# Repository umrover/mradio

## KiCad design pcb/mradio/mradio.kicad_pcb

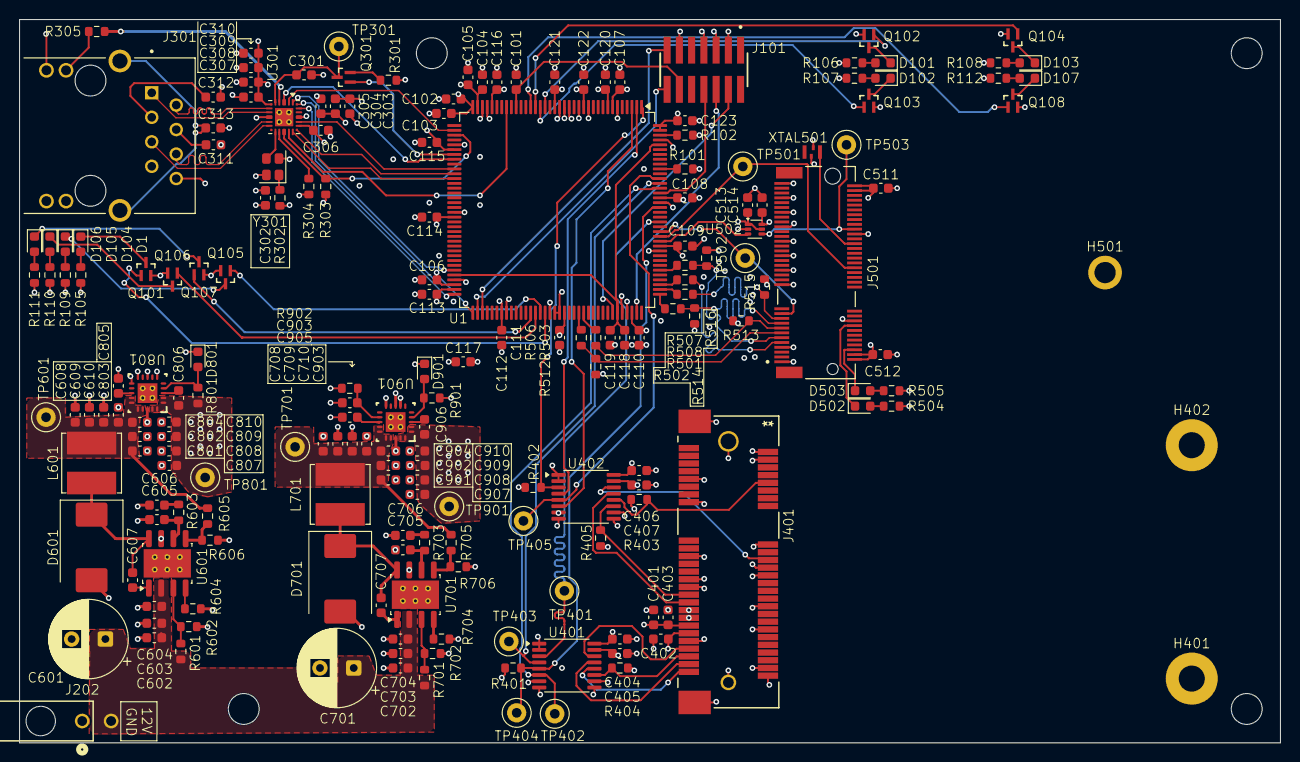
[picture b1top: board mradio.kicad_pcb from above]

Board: 6 copper layers, 130.8 x 75.0 mm, 193 parts (0 on the bottom side), 122 nets.

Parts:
C101, C102, C104, C107, C108, C109, C110, C111, C112, C113, C114, C115, C116, C121, C122, C123, C305, C308, C403, C404, C405, C406, C407, C805, C905: 100nF; C_0603_1608Metric
C103, C105, C120, C304, C309, C402: 1uF; C_0603_1608Metric
C106, C117: 4.7uF; C_0603_1608Metric
C118, C119, C602, C603, C604, C702, C703, C704: 2.2uF; C_0603_1608Metric
C301: 0.01uF; C_0603_1608Metric
C302, C311, C312, C513, C514, C607, C707: 0.1uF; C_0603_1608Metric
C303, C310, C511, C512, C802, C803, C804, C808, C809, C810, C902, C903, C903#2, C904, C908, C909, C910: 10uF; C_0603_1608Metric
C306, C307, C806, C906: 10nF; C_0603_1608Metric
C313: 0nF; C_0603_1608Metric
C401, C608, C609, C610, C708, C709, C710, C801, C807, C901, C907: 47uF; C_0603_1608Metric
C601, C701: 100uF; CP_Radial_D8.0mm_P3.50mm
C605: 100pF; C_0603_1608Metric
C606, C706: 29nF; C_0603_1608Metric
C705: 180pF; C_0603_1608Metric
D1, D101, D102, D103, D104, D105, D106, D107, D502, D503, D801, D901: LED; LED_0603_1608Metric
D601, D701: 60V; D_SMC
H401, H402: MountingHole_Pad; MountingHole_2.7mm_M2.5_Pad
H501: MountingHole_Pad; MountingHole_2.2mm_M2_ISO7380_Pad
J101: Conn_02x07_Odd_Even; SAMTEC_FTSH-107-01-X-DV-K
J202: Conn_01x02; CONN_2125280000_02_MOL
J301: 2250065-1; BEL_2250065-1
J401: MM60-52B1-E1-R650; CONN_MM60-52B1-E1-R650_JAE
J501: MDT420E01001; AMPHENOL_MDT420E01001
L601, L701: 10uH; L_Bourns_SRN6045TA
Q101, Q102, Q103, Q104, Q105, Q106, Q107, Q108: Q_NMOS; SSM_TOS_REAL
Q301: SSM3K56FS_LF; SSM_TOS
R101, R102, R401, R402, R403, R404, R405, R512, R513, R514, R515, R516: 10K; R_0603_1608Metric
R105, R106, R107, R108, R109, R110, R111, R112, R504, R505: 1K; R_0603_1608Metric
R301, R501, R502, R503, R506, R507, R508, R902: 0; R_0603_1608Metric
R302: 70k; R_0603_1608Metric
R303: 2.2k; R_0603_1608Metric
R304: 6.49k; R_0603_1608Metric
R305: 250; R_0603_1608Metric
R601, R701: 442k; R_0603_1608Metric
R602, R702: 90.9k; R_0603_1608Metric
R603: 6.34k; R_0603_1608Metric
R604, R704: 193k; R_0603_1608Metric
R605: 37k; R_0603_1608Metric
R606, R706: 10.2k; R_0603_1608Metric
R703: 3.74k; R_0603_1608Metric
R705: 17.4k; R_0603_1608Metric
R801, R901: 1.2k; R_0603_1608Metric
TP301, TP401, TP402, TP403, TP404, TP405, TP501, TP502, TP503: TestPoint; TestPoint_Loop_D1.80mm_Drill1.0mm_Beaded
TP601: 3v7_TP; TestPoint_Loop_D1.80mm_Drill1.0mm_Beaded
TP701: 2v2_TP; TestPoint_Loop_D1.80mm_Drill1.0mm_Beaded
TP801: 3v3_TP; TestPoint_Loop_D1.80mm_Drill1.0mm_Beaded
TP901: 1v8_TP; TestPoint_Loop_D1.80mm_Drill1.0mm_Beaded
U1: STM32H745ZITx; LQFP-144_20x20mm_P0.5mm
U301: DP83825I; Texas_RMQ0024A_WQFN-24-1EP_3x3mm_P0.4mm_EP1.9x1.9mm
U401, U402: 74AVC4T774; TSSOP-16_4.4x5mm_P0.65mm
U502: SN74LVC1T45DRL; SOT-563
U601, U701: TPS54560BDDA; Texas_R-PDSO-G8_EP2.95x4.9mm_Mask2.4x3.1mm_ThermalVias
U801, U901: TPS7A8500ARGRR; TPS7A8500RGRR
XTAL501: SIT1533AI-H4-DCC-32.768E; XTAL4_SiT1533_SIT
Y301: DSC1525JL2A-25M00000T; Oscillator_SMD_SeikoEpson_SG210-4Pin_2.5x2.0mm

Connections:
+1V8: C102.1, C103.1, C104.1, C105.1, C106.2, C107.1, C108.1, C109.1, C110.1, C111.1, C112.1, C113.1, C114.1, C115.1, C116.1, C117.1, C120.1, C121.1, C122.1, C123.1, C302.1, C303.2, C304.2, C305.2, C306.2, C404.1, C406.1, C513.1, C906.1, C907.1, C908.1, C909.1, C910.1, J101.3, R102.2, R302.1, R303.1, R401.1, R402.1, R512.1, R513.1, R514.1, R515.1, R516.1, TP901.1 (1_1), U1.7 (VDD), U1.8 (VBAT), U1.13 (VDD), U1.19 (VDD), U1.32 (VDD), U1.35 (VREF+), U1.36 (VDDA), U1.42 (VDD), U1.56 (VDD), U1.70 (VDDLDO), U1.71 (VDD), U1.79 (VDD), U1.92 (VDD), U1.105 (VDDLDO), U1.106 (VDD), U1.119 (VDD), U1.129 (VDD), U1.143 (VDDLDO), U1.144 (VDD), U301.19 (VDDIO), U401.1 (DIR1), U401.2 (DIR2), U401.7 (DIR3), U401.16 (V_{CCA}), U402.1 (DIR1), U402.2 (DIR2), U402.16 (V_{CCA}), U502.1 (VCCA), U502.5 (DIR), U901.1 (OUT), U901.2 (SNS), U901.19 (OUT), U901.20 (OUT), Y301.4 (Vcc)
+2V2: C708.1, C709.1, C710.1, C901.1, C902.1, C903#2.1, C904.1, L701.2, R705.1, TP701.1 (1_1), U901.14 (EN), U901.15 (IN), U901.16 (IN), U901.17 (IN)
+3V3: C307.2, C308.2, C309.2, C310.2, C401.1, C402.1, C403.1, C405.1, C407.1, C511.1, C512.1, C514.2, C806.1, C807.1, C808.1, C809.1, C810.1, J401.2 (+3V3AUX), J401.24 (+3V3AUX), J401.39 (+3V3AUX), J401.41 (+3V3AUX), J401.52 (+3V3AUX), J501.2, J501.4, J501.72, J501.74, R105.2, R106.2, R107.2, R108.2, R109.2, R110.2, R111.2, R112.2, R403.1, R404.1, R504.1, R505.1, R801.2, R901.2, R902.1, TP801.1 (1_1), U1.90 (VDD50_USB), U1.91 (VDD33_USB), U301.6 (VDDA3V3), U401.15 (V_{CCB}), U402.15 (V_{CCB}), U502.6 (VCCB), U801.1 (OUT), U801.2 (SNS), U801.19 (OUT), U801.20 (OUT), XTAL501.4 (Vdd)
+3V7: C608.1, C609.1, C610.1, C801.1, C802.1, C803.1, C804.1, L601.2, R605.1, TP601.1 (1_1), U801.14 (EN), U801.15 (IN), U801.16 (IN), U801.17 (IN)
+12V: C601.1, C602.1, C603.1, C604.1, C701.1, C702.1, C703.1, C704.1, J202.2, R601.1, R701.1, U601.2 (VIN), U701.2 (VIN)
/2.4-5 Ghz/M2_WL_REG_ON: J501.56, TP503.1 (1_1), U502.4 (B)
/2.4-5 Ghz/SDIO_CK: J501.9, R508.1
/2.4-5 Ghz/SDIO_CMD: J501.11, R507.1, R516.2
/2.4-5 Ghz/SDIO_D0: J501.13, R506.1, R512.2
/2.4-5 Ghz/SDIO_D1: J501.15, R503.1, R513.2
/2.4-5 Ghz/SDIO_D2: J501.17, R502.1, R514.2
/2.4-5 Ghz/SDIO_D3: J501.19, R501.1, R515.2
/900 Mhz/SPI1_CS_3V3: J401.51 (Reserved), U401.12 (B3)
/900 Mhz/SPI1_MISO_3V3: J401.47 (Reserved), R404.2, U401.11 (B4)
/900 Mhz/SPI1_MOSI_3V3: J401.49 (Reserved), U401.13 (B2)
/900 Mhz/SPI1_SCK_3V3: J401.45 (Reserved), U401.14 (B1)
/900 Mhz/SPI_INT_3V3: J401.10 (UIM_DATA), R403.2, U402.12 (B3)
/900 Mhz/WM_BUSY_3V3: J401.31 (PETn0), R405.2, U402.11 (B4)
/900 Mhz/WM_RESET_3V3: J401.22 (~PERST), U402.14 (B1)
/900 Mhz/WM_WAKE_3V3: J401.33 (PETp0), U402.13 (B2)
/Ethernet/ETH_LINK: R305.2, U301.4 (LED0/S(ANEG_Dis))
/Ethernet/ETH_RD+: J301.1 (RDP), U301.8 (RD+)
/Ethernet/ETH_RD-: J301.2 (RDN), U301.7 (RD-)
/Ethernet/ETH_TD+: J301.5 (TDP), U301.11 (TD+)
/Ethernet/ETH_TD-: J301.6 (TDN), U301.10 (TD-)
/MCU/BOOT0: R101.1, U1.135 (BOOT0)
/MCU/M4_DBG1: Q102.G, U1.21 (PF7)
/MCU/M4_DBG2: Q103.G, U1.22 (PF8)
/MCU/M7_DBG1: Q104.G, U1.23 (PF9)
/MCU/M7_DBG2: Q108.G, U1.24 (PF10)
/MCU/NRST: C101.1, J101.12, U1.27 (NRST)
/MCU/STLINK_RX: J101.13, U1.75 (PB15)
/MCU/STLINK_TX: J101.14, U1.74 (PB14)
/MCU/SWCLK: J101.6, U1.107 (PA14)
/MCU/SWDIO: J101.4, U1.102 (PA13)
/MCU/SWO: J101.8, U1.130 (PB3)
/MCU/SoS_LED1: Q107.G, U1.85 (PD15)
/MCU/SoS_LED2: Q106.G, U1.86 (PG6)
/MCU/SoS_LED3: Q105.G, U1.87 (PG7)
/MCU/SoS_LED4: Q101.G, U1.88 (PG8)
/MCU/VCAP: C118.1, C119.1, U1.68 (VCAP), U1.103 (VCAP), U1.140 (VCAP)
/Power Distribution/2v2_Buck/FB: R705.2, R706.1, U701.5 (FB)
/Power Distribution/3v7_Buck/FB: R605.2, R606.1, U601.5 (FB)
ETH_CRS_DV: U1.46 (PA7), U301.20 (CRS_DV/S(PhyAdd[1]))
ETH_INT: U1.44 (PA5), U301.3 (INTR/~PWRDN)
ETH_MDC: U1.29 (PC1), U301.16 (MDC)
ETH_MDIO: R303.2, U1.39 (PA2), U301.15 (MDIO)
ETH_REF_CLK: U1.38 (PA1), U301.2 (50MHzOut/LED2/S(RX_DV_EN))
ETH_RESET: Q301.1 (G), U1.43 (PA4)
ETH_RXD0: U1.47 (PC4), U301.18 (RX_D0/S(PhyAdd[0]))
ETH_RXD1: U1.48 (PC5), U301.17 (RX_D1/S(Master/Slave))
ETH_TXD0: U1.72 (PB12), U301.23 (TX_D0)
ETH_TXD1: U1.73 (PB13), U301.24 (TX_D1)
ETH_TX_EN: U1.67 (PB11), U301.1 (TX_EN)
GND: C101.2, C102.2, C103.2, C104.2, C105.2, C106.1, C107.2, C108.2, C109.2, C110.2, C111.2, C112.2, C113.2, C114.2, C115.2, C116.2, C117.2, C118.2, C119.2, C120.2, C121.2, C122.2, C123.2, C301.2, C302.2, C303.1, C304.1, C305.1, C306.1, C307.1, C308.1, C309.1, C310.1, C311.1, C312.1, C313.2, C401.2, C402.2, C403.2, C404.2, C405.2, C406.2, C407.2, C511.2, C512.2, C513.2, C514.1, C601.2, C602.2, C603.2, C604.2, C605.2, C606.2, C608.2, C609.2, C610.2, C701.2, C702.2, C703.2, C704.2, C705.2, C706.2, C708.2, C709.2, C710.2, C801.2, C802.2, C803.2, C804.2, C805.2, C807.2, C808.2, C809.2, C810.2, C901.2, C902.2, C903.2, C903#2.2, C904.2, C905.2, C907.2, C908.2, C909.2, C910.2, D601.2 (A), D701.2 (A), D801.1 (K), D901.1 (K), H401.1 (1_1), H402.1 (1_1), H501.1 (1_1), J101.5, J101.7, J101.11, J202.1, J301.8 (GND), J301.10, J401.4 (GND), J401.9 (GND), J401.15 (GND), J401.18 (GND), J401.21 (GND), J401.26 (GND), J401.27 (GND), J401.29 (GND), J401.34 (GND), J401.35 (GND), J401.37 (GND), J401.40 (GND), J401.43 (GND), J401.50 (GND), J401.MP, J501.1, J501.7, J501.18, J501.33, J501.39, J501.45, J501.51, J501.54, J501.57, J501.63, J501.69, J501.75, Q101.S, Q102.S, Q103.S, Q104.S, Q105.S, Q106.S, Q107.S, Q108.S, R101.2, R301.2, R304.2, R405.1, R602.2, R604.2, R606.2, R702.2, R704.2, R706.2, U1.6 (VSS), U1.12 (VSS), U1.14 (VSSSMPS), U1.16 (VDDSMPS), U1.17 (VFBSMPS), U1.18 (VSS), U1.33 (VSS), U1.34 (VSSA), U1.41 (VSS), U1.55 (VSS), U1.69 (VSS), U1.80 (VSS), U1.89 (VSS), U1.104 (VSS), U1.118 (VSS), U1.128 (VSS), U1.141 (VSS), U301.9 (GND), U301.21 (GND), U301.25 (GND), U401.8 (DIR4), U401.9 (~OE), U401.10 (GND), U402.7 (DIR3), U402.8 (DIR4), U402.9 (~OE), U402.10 (GND), U502.2 (GND), U601.7 (GND), U601.9 (GND), U701.7 (GND), U701.9 (GND), U801.6 (100_mV), U801.8 (GND), U801.10 (800_mV), U801.11 (1.6_V), U801.18 (GND), U801.21 (PAD), U901.7 (200_mV), U901.8 (GND), U901.10 (800_mV), U901.18 (GND), U901.21 (PAD), XTAL501.2 (GND), Y301.2 (GND)
unnamed: C606.1, R603.1
unnamed: C706.1, R703.1
unnamed: D1.2 (A), R105.1
unnamed: D1.1 (K), Q101.D
unnamed: D101.2 (A), R106.1
unnamed: D101.1 (K), Q102.D
unnamed: D102.2 (A), R107.1
unnamed: D102.1 (K), Q103.D
unnamed: D103.2 (A), R108.1
unnamed: D103.1 (K), Q104.D
unnamed: D104.2 (A), R109.1
unnamed: D104.1 (K), Q105.D
unnamed: D105.2 (A), R110.1
unnamed: D105.1 (K), Q106.D
unnamed: D106.2 (A), R111.1
unnamed: D106.1 (K), Q107.D
unnamed: D107.2 (A), R112.1
unnamed: D107.1 (K), Q108.D
unnamed: D502.2 (A), R504.2
unnamed: D502.1 (K), J501.16
unnamed: D503.2 (A), R505.2
unnamed: D503.1 (K), J501.6
unnamed: C607.2, D601.1 (K), L601.1, U601.8 (SW)
unnamed: C707.2, D701.1 (K), L701.1, U701.8 (SW)
unnamed: D801.2 (A), R801.1, U801.4 (PG)
unnamed: D901.2 (A), R901.1, U901.4 (PG)
unnamed: J301.9, R305.1
unnamed: C312.2, J301.3 (RCT)
unnamed: C313.1, J301.SH1 (SHIELD), J301.SH2 (SHIELD__1)
unnamed: C311.2, J301.4 (TCT)
unnamed: C301.1, Q301.3 (D), TP301.1 (1_1), U301.5 (~RST)
unnamed: Q301.2 (S), R301.1
unnamed: R102.1, U1.142 (PDR_ON)
unnamed: R304.1, U301.14 (RBIAS)
unnamed: U301.13 (XI/50MHzIn), Y301.3 (OUT)
unnamed: C607.1, U601.1 (BOOT)
unnamed: C605.1, R603.2, U601.6 (COMP)
unnamed: R601.2, R602.1, U601.3 (EN)
unnamed: R604.1, U601.4 (RT/CLK)
unnamed: C707.1, U701.1 (BOOT)
unnamed: C705.1, R703.2, U701.6 (COMP)
unnamed: R701.2, R702.1, U701.3 (EN)
unnamed: R704.1, U701.4 (RT/CLK)
unnamed: C806.2, U801.3 (FB)
unnamed: C805.1, U801.13 (NR_SS)
unnamed: C903.1, R902.2, U901.12 (BIAS)
unnamed: C906.2, U901.3 (FB)
unnamed: C905.1, U901.13 (NR_SS)
unnamed: J501.50, XTAL501.3 (CLK_Out)
unnamed: R302.2, Y301.1 (OE)
SDMMC1_CK: R508.2, U1.111 (PC12)
SDMMC1_CMD: R507.2, U1.114 (PD2)
SDMMC1_D0: R506.2, U1.95 (PC8)
SDMMC1_D1: R503.2, U1.96 (PC9)
SDMMC1_D2: R502.2, U1.109 (PC10)
SDMMC1_D3: R501.2, U1.110 (PC11)
SPI1_CS: R401.2, TP404.1 (1_1), U1.127 (PG14), U401.5 (A3)
SPI1_MISO: TP402.1 (1_1), U1.131 (PB4), U401.6 (A4)
SPI1_MOSI: TP403.1 (1_1), U1.132 (PB5), U401.4 (A2)
SPI1_SCK: TP401.1 (1_1), U1.124 (PG11), U401.3 (A1)
SPI_INT: TP405.1 (1_1), U1.133 (PB6), U402.5 (A3)
WL_DEV_WAKE: J501.40, TP501.1 (1_1), U1.121 (PD7)
WL_HOST_WAKE: J501.21, TP502.1 (1_1), U1.122 (PG9)
WL_REG_ON: U1.120 (PD6), U502.3 (A)
WM_BUSY: U1.3 (PE4), U402.6 (A4)
WM_RESET: R402.2, U1.1 (PE2), U402.3 (A1)
WM_WAKE: U1.2 (PE3), U402.4 (A2)

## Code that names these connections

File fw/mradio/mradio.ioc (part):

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Mcu.Name=STM32H745ZITx
Mcu.Package=LQFP144
Mcu.UserName=STM32H745ZITx
PA1.GPIOParameters=PinAttribute,GPIO_Speed_Default_HIGH
PA1.GPIO_Speed_Default_HIGH=GPIO_SPEED_FREQ_VERY_HIGH
PA1.Mode=RMII
PA1.PinAttribute=CortexM7
PA1.Signal=ETH_REF_CLK
PA13\ (JTMS/SWDIO).Signal=DEBUG_JTMS-SWDIO
PA14\ (JTCK/SWCLK).Signal=DEBUG_JTCK-SWCLK
PA2.GPIOParameters=PinAttribute,GPIO_Speed_Default_HIGH
PA2.GPIO_Speed_Default_HIGH=GPIO_SPEED_FREQ_VERY_HIGH
PA2.Mode=RMII
PA2.PinAttribute=CortexM7
PA2.Signal=ETH_MDIO
PA4.ContextOwner=CortexM7
PA4.GPIOParameters=GPIO_Speed,PinState,GPIO_Label,PinAttribute
PA4.GPIO_Label=ETH_RESET
PA4.GPIO_Speed=GPIO_SPEED_FREQ_HIGH
PA4.PinAttribute=CortexM7
PA4.PinState=GPIO_PIN_RESET
PA4.Signal=GPIO_Output
PA5.ContextOwner=CortexM7
PA5.GPIOParameters=GPIO_PuPd,GPIO_Label,GPIO_ModeDefaultEXTI,PinAttribute
PA5.GPIO_Label=ETH_INT
PA5.GPIO_ModeDefaultEXTI=GPIO_MODE_IT_FALLING
PA5.GPIO_PuPd=GPIO_PULLUP
PA5.PinAttribute=CortexM7
PA5.Signal=GPXTI5
PA7.GPIOParameters=PinAttribute,GPIO_Speed_Default_HIGH
PA7.GPIO_Speed_Default_HIGH=GPIO_SPEED_FREQ_VERY_HIGH
PA7.Mode=RMII
PA7.PinAttribute=CortexM7
PA7.Signal=ETH_CRS_DV
PB11.GPIOParameters=PinAttribute,GPIO_Speed_Default_HIGH
PB11.GPIO_Speed_Default_HIGH=GPIO_SPEED_FREQ_VERY_HIGH
PB11.Mode=RMII
PB11.PinAttribute=CortexM7
PB11.Signal=ETH_TX_EN
PB12.GPIOParameters=PinAttribute,GPIO_Speed_Default_HIGH
PB12.GPIO_Speed_Default_HIGH=GPIO_SPEED_FREQ_VERY_HIGH
PB12.Mode=RMII
PB12.PinAttribute=CortexM7
PB12.Signal=ETH_TXD0
PB13.GPIOParameters=PinAttribute,GPIO_Speed_Default_HIGH
PB13.GPIO_Speed_Default_HIGH=GPIO_SPEED_FREQ_VERY_HIGH
PB13.Mode=RMII
PB13.PinAttribute=CortexM7
PB13.Signal=ETH_TXD1
PB14.GPIOParameters=GPIO_Label,PinAttribute
PB14.GPIO_Label=STLINK_TX
PB14.Mode=Asynchronous
PB14.PinAttribute=CortexM4
PB14.Signal=USART1_TX
PB15.GPIOParameters=GPIO_Label,PinAttribute
PB15.GPIO_Label=STLINK_RX
PB15.Mode=Asynchronous
PB15.PinAttribute=CortexM4
PB15.Signal=USART1_RX
PB3\ (JTDO/TRACESWO).Signal=DEBUG_JTDO-SWO
PB4\ (NJTRST).GPIOParameters=PinAttribute
PB4\ (NJTRST).Mode=Full_Duplex_Master
PB4\ (NJTRST).PinAttribute=CortexM4
PB4\ (NJTRST).Signal=SPI1_MISO
PB5.GPIOParameters=GPIO_Speed,GPIO_Label,PinAttribute
PB5.GPIO_Label=SPI1_MOSI
PB5.GPIO_Speed=GPIO_SPEED_FREQ_HIGH
PB5.Mode=Full_Duplex_Master
PB5.PinAttribute=CortexM4
PB5.Signal=SPI1_MOSI
PB6.ContextOwner=CortexM4
PB6.GPIOParameters=GPIO_PuPd,GPIO_Label,GPIO_ModeDefaultEXTI,PinAttribute
PB6.GPIO_Label=SPI_INT
PB6.GPIO_ModeDefaultEXTI=GPIO_MODE_IT_FALLING
PB6.GPIO_PuPd=GPIO_PULLUP
PB6.PinAttribute=CortexM4
PB6.Signal=GPXTI6
PC1.GPIOParameters=PinAttribute,GPIO_Speed_Default_HIGH
PC1.GPIO_Speed_Default_HIGH=GPIO_SPEED_FREQ_VERY_HIGH
PC1.Mode=RMII
PC1.PinAttribute=CortexM7
PC1.Signal=ETH_MDC
PC10.GPIOParameters=PinAttribute
PC10.Mode=SD_4_bits_Wide_bus
PC10.PinAttribute=CortexM4
PC10.Signal=SDMMC1_D2
PC11.GPIOParameters=PinAttribute
PC11.Mode=SD_4_bits_Wide_bus
PC11.PinAttribute=CortexM4
PC11.Signal=SDMMC1_D3
PC12.GPIOParameters=PinAttribute
PC12.Mode=SD_4_bits_Wide_bus
PC12.PinAttribute=CortexM4
PC12.Signal=SDMMC1_CK
PC4.GPIOParameters=PinAttribute,GPIO_Speed_Default_HIGH
PC4.GPIO_Speed_Default_HIGH=GPIO_SPEED_FREQ_VERY_HIGH
PC4.Mode=RMII
PC4.PinAttribute=CortexM7
PC4.Signal=ETH_RXD0
PC5.GPIOParameters=PinAttribute,GPIO_Speed_Default_HIGH
PC5.GPIO_Speed_Default_HIGH=GPIO_SPEED_FREQ_VERY_HIGH
PC5.Mode=RMII
PC5.PinAttribute=CortexM7
PC5.Signal=ETH_RXD1
PC8.GPIOParameters=PinAttribute
PC8.Mode=SD_4_bits_Wide_bus
PC8.PinAttribute=CortexM4
PC8.Signal=SDMMC1_D0
PC9.GPIOParameters=PinAttribute
PC9.Mode=SD_4_bits_Wide_bus
PC9.PinAttribute=CortexM4
PC9.Signal=SDMMC1_D1
PD15.ContextOwner=CortexM4
PD15.GPIOParameters=GPIO_Label,PinAttribute
PD15.GPIO_Label=SoS_LED1
PD15.PinAttribute=CortexM4
PD15.Signal=GPIO_Output
PD2.GPIOParameters=PinAttribute
PD2.Mode=SD_4_bits_Wide_bus
PD2.PinAttribute=CortexM4
PD2.Signal=SDMMC1_CMD
PD6.ContextOwner=CortexM4
PD6.GPIOParameters=GPIO_Label,PinAttribute
PD6.GPIO_Label=WL_REG_ON
PD6.PinAttribute=CortexM4
PD6.Signal=GPIO_Output
PD7.ContextOwner=CortexM4
PD7.GPIOParameters=GPIO_Label,PinAttribute
PD7.GPIO_Label=WL_DEV_WAKE
PD7.PinAttribute=CortexM4
PD7.Signal=GPIO_Output
PE2.ContextOwner=CortexM4
PE2.GPIOParameters=GPIO_Label,PinAttribute
PE2.GPIO_Label=WM_RESET
PE2.PinAttribute=CortexM4
PE2.Signal=GPIO_Output
PE3.ContextOwner=CortexM4
PE3.GPIOParameters=GPIO_Speed,GPIO_Label,PinAttribute
PE3.GPIO_Label=WM_WAKE
PE3.GPIO_Speed=GPIO_SPEED_FREQ_HIGH
PE3.PinAttribute=CortexM4
PE3.Signal=GPIO_Output
PE4.ContextOwner=CortexM4
PE4.GPIOParameters=GPIO_PuPd,GPIO_Label,PinAttribute
PE4.GPIO_Label=WM_BUSY
PE4.GPIO_PuPd=GPIO_PULLDOWN
PE4.PinAttribute=CortexM4
PE4.Signal=GPIO_Input
PF10.ContextOwner=CortexM7
PF10.GPIOParameters=GPIO_Label,PinAttribute
PF10.GPIO_Label=M7_DBG2
PF10.PinAttribute=CortexM7
PF10.Signal=GPIO_Output
PF7.ContextOwner=CortexM4
PF7.GPIOParameters=GPIO_Label,PinAttribute
PF7.GPIO_Label=M4_DBG1
PF7.PinAttribute=CortexM4
PF7.Signal=GPIO_Output
PF8.ContextOwner=CortexM4
PF8.GPIOParameters=GPIO_Label,PinAttribute
PF8.GPIO_Label=M4_DBG2
PF8.PinAttribute=CortexM4
PF8.Signal=GPIO_Output
PF9.ContextOwner=CortexM7
PF9.GPIOParameters=GPIO_Label,PinAttribute
PF9.GPIO_Label=M7_DBG1
PF9.PinAttribute=CortexM7
PF9.Signal=GPIO_Output
PG11.GPIOParameters=GPIO_Speed,PinAttribute
PG11.GPIO_Speed=GPIO_SPEED_FREQ_HIGH
PG11.Mode=Full_Duplex_Master
PG11.PinAttribute=CortexM4
PG11.Signal=SPI1_SCK
PG14.ContextOwner=CortexM4
PG14.GPIOParameters=PinState,GPIO_Label,PinAttribute
PG14.GPIO_Label=SPI1_CS
PG14.PinAttribute=CortexM4
PG14.PinState=GPIO_PIN_SET
PG14.Signal=GPIO_Output
PG6.ContextOwner=CortexM4
PG6.GPIOParameters=GPIO_Label,PinAttribute
PG6.GPIO_Label=SoS_LED2
PG6.PinAttribute=CortexM4
PG6.Signal=GPIO_Output
PG7.ContextOwner=CortexM4
PG7.GPIOParameters=GPIO_Label,PinAttribute
PG7.GPIO_Label=SoS_LED3
PG7.PinAttribute=CortexM4
PG7.Signal=GPIO_Output
PG8.ContextOwner=CortexM4
PG8.GPIOParameters=GPIO_Label,PinAttribute
PG8.GPIO_Label=SoS_LED4
PG8.PinAttribute=CortexM4
PG8.Signal=GPIO_Output
PG9.ContextOwner=CortexM4
PG9.GPIOParameters=GPIO_Label,PinAttribute
PG9.GPIO_Label=WL_HOST_WAKE
PG9.PinAttribute=CortexM4
PG9.Signal=GPXTI9
RCC.SYSCLKFreq_VALUE=400000000
RCC.SYSCLKSource=RCC_SYSCLKSOURCE_PLLCLK
board=custom
